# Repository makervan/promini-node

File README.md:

# ProMini LoRaWAN Node
A LoRaWAN node based on the Arduino ProMini and the RFM95 LoRa module. Based on the original design by [Doug Larue](https://github.com/dlarue/KiCAD/tree/master/ProMini-LoRaWAN-node), but with some additional options:

* u.FL antenna connector
* Grove connector for I2C (can also be used for analog or digital signals)
* Circuitry to measure battery voltage

## Parts
* Arduino Pro Mini 3.3V, 8 Mhz
* RFM95 module (frequency band based on your location)
* Pin headers
* Edge-mounted SMA connector (e.g. [this part](https://www.digikey.com/product-detail/en/rf-solutions/CON-SMA-EDGE-S/CON-SMA-EDGE-S-ND/5845767)) or wire-antenna of correct length

## Additional information
* Board can be powered directly from 2 AA batteries to the 3.3V input
* [Full tutorial using this board by Frank Beks](https://www.thethingsnetwork.org/labs/story/creating-a-ttn-node)

## License
* Licensed under Creative Commons Attribution-ShareAlike 4.0 Unported License (CC BY-SA 4.0)
* Original work by [Doug Larue](https://github.com/dlarue)
* Modifications by [Severin Schols](https://github.com/tiefpunkt)

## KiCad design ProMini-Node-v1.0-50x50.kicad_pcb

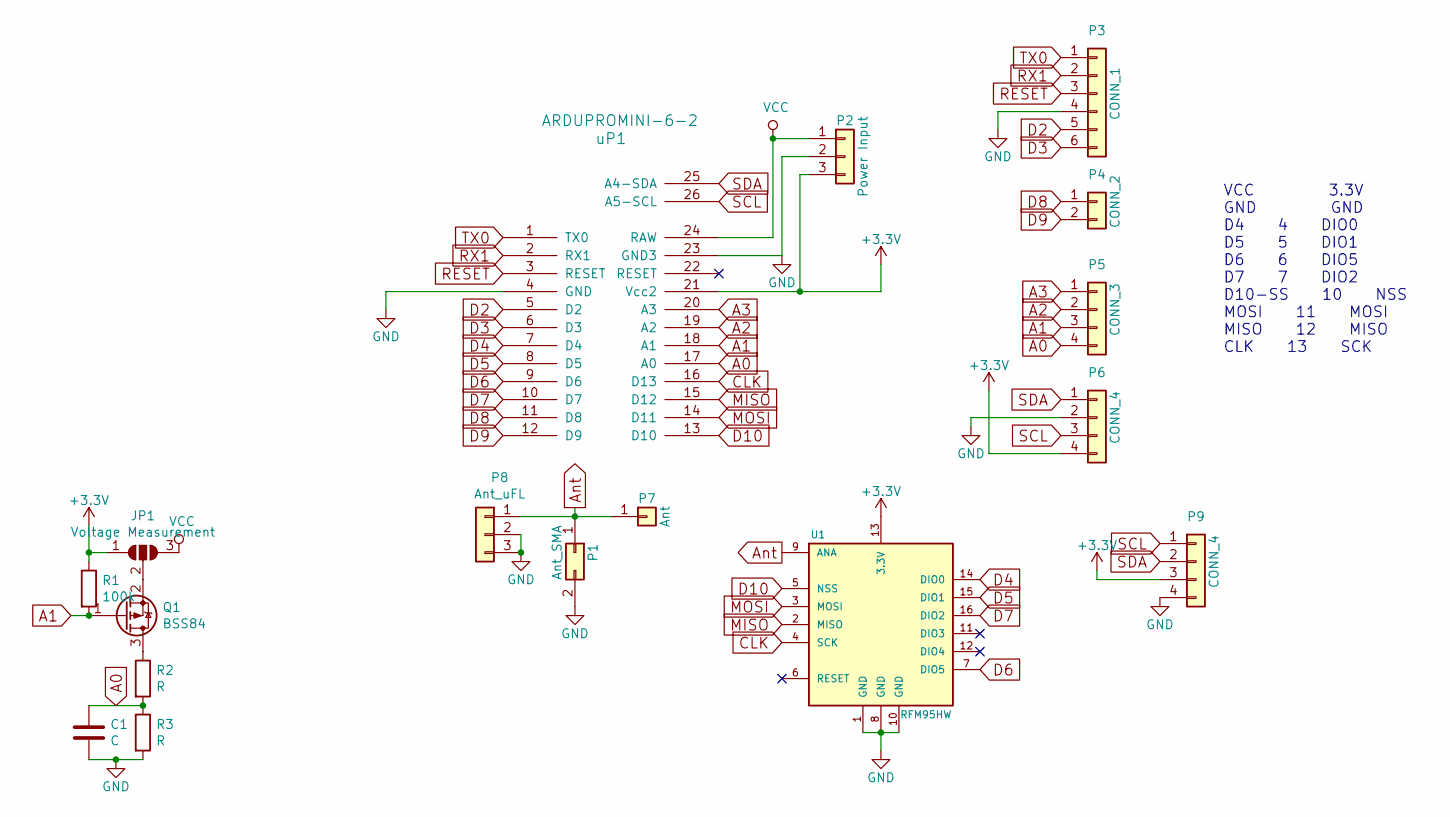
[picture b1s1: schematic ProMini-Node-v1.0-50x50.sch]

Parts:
C1: C; C_0805_2012Metric_Pad1.15x1.40mm_HandSolder
JP1: Voltage Measurement; SolderJumper-3_P1.3mm_Open_RoundedPad1.0x1.5mm_NumberLabels
P1: Ant_SMA; SMA_EDGE
P2: Power Input; PINHEAD1-3
P3: CONN_1; Pin_Header_Straight_1x06
P4: CONN_2; Pin_Header_Straight_1x02
P5: CONN_3; Pin_Header_Straight_1x04
P6: CONN_4; Pin_Header_Straight_1x04
P7: Ant; PINTST
P8: Ant_uFL; U.FL-COAX
P9: CONN_4; NS-Tech_Grove_1x04_P2mm_Vertical
Q1: BSS84; SOT-23
R1: 100k; R_0805_2012Metric_Pad1.15x1.40mm_HandSolder
R2, R3: R; R_0805_2012Metric_Pad1.15x1.40mm_HandSolder
U1: RFM95HW; RFM69HW_SMD_Handsoldering-Narrow
uP1: ARDUPROMINI-6-2; pro_mini-26

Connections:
+3V3: JP1.1 (A), P2.3, P6.4, P9.3, R1.1, U1.13 (3.3V), uP1.21 (Vcc2)
A0: C1.1, P5.4, R2.2, R3.1, uP1.17 (A0)
A1: P5.3, Q1.1 (G), R1.2, uP1.18 (A1)
A2: P5.2, uP1.19 (A2)
A3: P5.1, uP1.20 (A3)
Ant: P1.1, P7.1, P8.1, U1.9 (ANA)
CLK: U1.4 (SCK), uP1.16 (D13)
D2: P3.5, uP1.5 (D2)
D3: P3.6, uP1.6 (D3)
D4: U1.14 (DIO0), uP1.7 (D4)
D5: U1.15 (DIO1), uP1.8 (D5)
D6: U1.7 (DIO5), uP1.9 (D6)
D7: U1.16 (DIO2), uP1.10 (D7)
D8: P4.1, uP1.11 (D8)
D9: P4.2, uP1.12 (D9)
D10: U1.5 (NSS), uP1.13 (D10)
GND: C1.2, P1.2, P2.2, P3.4, P6.2, P8.2, P8.3, P9.4, R3.2, U1.1 (GND), U1.8 (GND), U1.10 (GND), uP1.4 (GND), uP1.23 (GND3)
MISO: U1.2 (MISO), uP1.15 (D12)
MOSI: U1.3 (MOSI), uP1.14 (D11)
unnamed: JP1.2 (C), Q1.2 (S)
unnamed: Q1.3 (D), R2.1
RESET: P3.3, uP1.3 (RESET)
RX1: P3.2, uP1.2 (RX1)
SCL: P6.3, P9.1, uP1.26 (A5-SCL)
SDA: P6.1, P9.2, uP1.25 (A4-SDA)
TX0: P3.1, uP1.1 (TX0)
VCC: JP1.3 (B), P2.1, uP1.24 (RAW)

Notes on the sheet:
VCC 3.3V GND GND D4 4 DIO0 D5 5 DIO1 D6 6 DIO5 D7 7 DIO2 D10-SS 10 NSS MOSI 11 MOSI MISO 12 MISO CLK 13 SCK

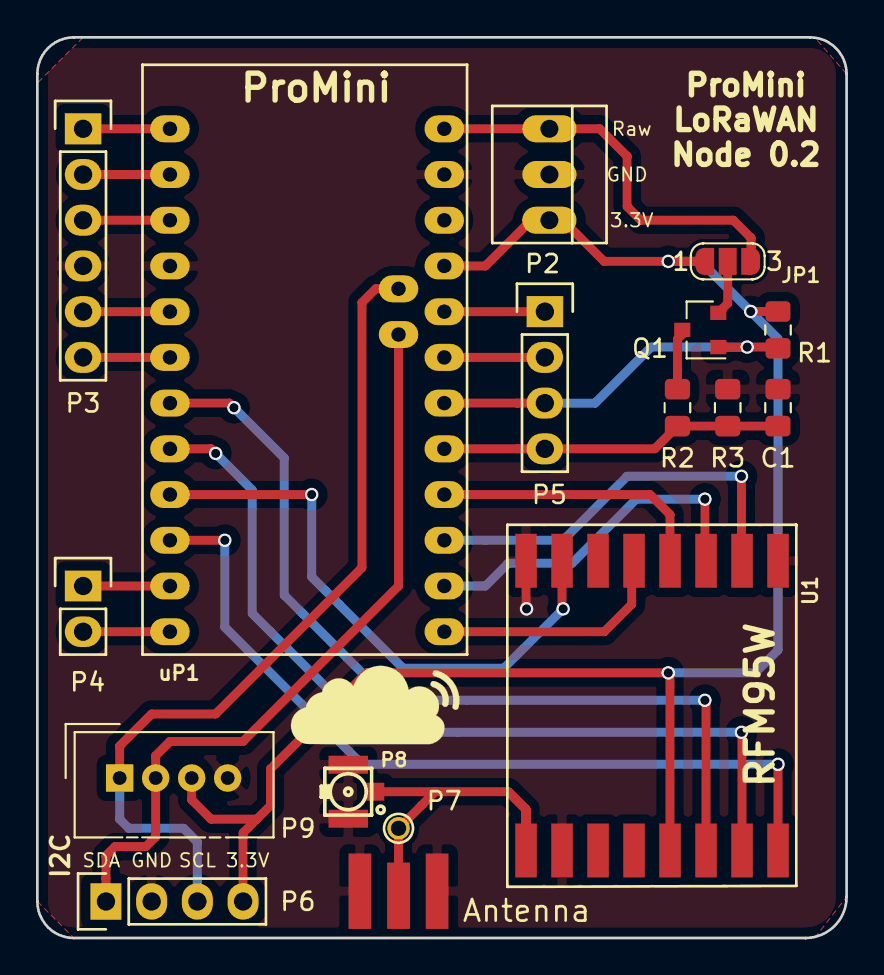
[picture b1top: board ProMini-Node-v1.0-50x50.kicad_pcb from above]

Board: 2 copper layers, 45.0 x 50.0 mm, 17 parts (0 on the bottom side), 27 nets.

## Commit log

2019-10-22 ProMini Node version 0.2, TTN Munich edition
    * Added uFL connector
    * Added Groove connector
    * Added battery voltage circuit
    * Added TTN logos etc.
    * README
